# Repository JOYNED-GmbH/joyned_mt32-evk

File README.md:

This is a hardware reference design for a fully compliant and certified Milan endpoint. It converts from a AVB/Milan network to I2S or TDM and vice versa.
Please feel free to copy and modify for your individual needs. This hardware reference design is published under the Creative Commons License. 

For software licensing visit www.joyned.io/oem-and-licensing

Product details: https://joyned.io/pages/mt32-oem-milan-endpoint

Portmap Spreadsheet: https://files.joyned.io/documents/mt32-evk/JOYNED_xCORE-200-Devices-Package-and-Portmap_AvbModule_MT32.xlsx

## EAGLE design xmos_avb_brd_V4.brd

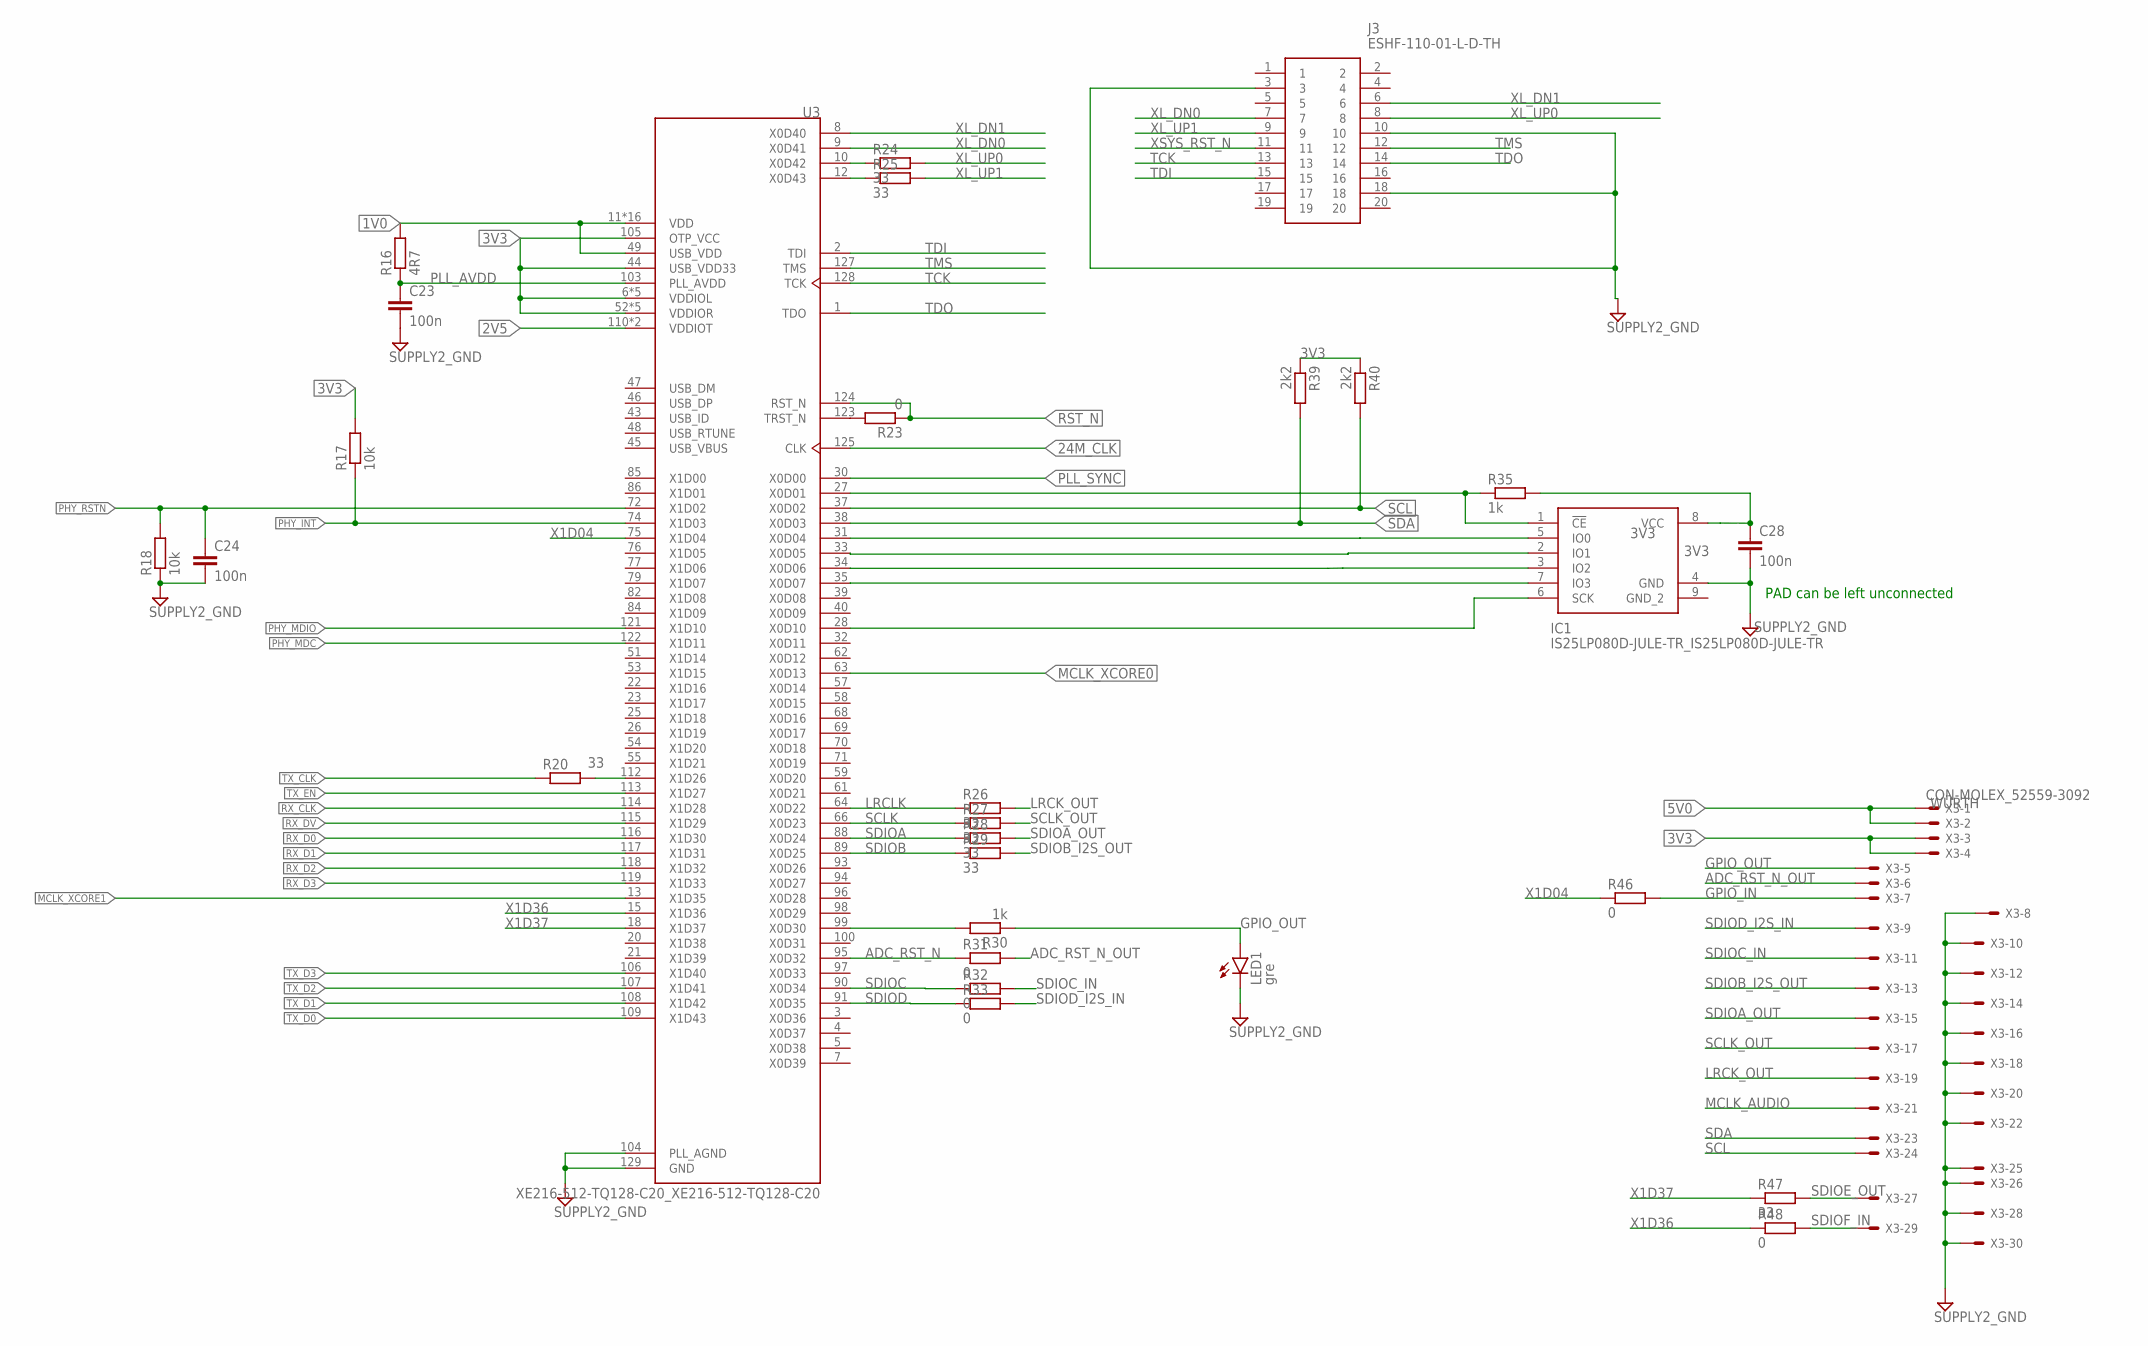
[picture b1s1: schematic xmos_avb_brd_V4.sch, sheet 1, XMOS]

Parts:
C23, C24, C28: 100n; RCL_C0402
IC1: IS25LP080D-JULE-TR_IS25LP080D-JULE-TR; IS25LP080D-JULE-TR_SON50P300X200X55-9N
J3: ESHF-110-01-L-D-TH; SHDR20W41P127_2X10_1905X559X54
LED1: gre; LED_CHIP-LED0603
R16: 4R7; RCL_R0402
R17, R18: 10k; RCL_R0402
R20, R24, R25, R26, R27, R28, R29, R47: 33; RCL_R0402
R23, R31, R32, R33, R46, R48: 0; RCL_R0402
R30, R35: 1k; RCL_R0402
R39, R40: 2k2; RCL_R0402
U3: XE216-512-TQ128-C20_XE216-512-TQ128-C20; XE216-512-TQ128-C20_QFP40P1600X1600X120-129N
X3: CON-MOLEX_52559-3092; MPN 687330124422

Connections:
1V0: R16.2, U3.11 (VDD), U3.16 (VDD), U3.17 (VDD), U3.24 (VDD), U3.36 (VDD), U3.41 (VDD), U3.49 (USB_VDD), U3.56 (VDD), U3.60 (VDD), U3.73 (VDD), U3.80 (VDD), U3.81 (VDD), U3.87 (VDD), U3.101 (VDD), U3.102 (VDD), U3.120 (VDD), U3.126 (VDD); also elsewhere on the board
2V5: U3.110 (VDDIOT), U3.111 (VDDIOT); also elsewhere on the board
3V3: C28.1, IC1.8 (VCC), R17.2, R35.2, R39.1, R40.1, U3.6 (VDDIOL), U3.14 (VDDIOL), U3.19 (VDDIOL), U3.29 (VDDIOL), U3.42 (VDDIOL), U3.44 (USB_VDD33), U3.52 (VDDIOR), U3.67 (VDDIOR), U3.78 (VDDIOR), U3.83 (VDDIOR), U3.92 (VDDIOR), U3.105 (OTP_VCC), X3.3, X3.4; also elsewhere on the board
5V0: X3.1, X3.2; also elsewhere on the board
24M_CLK: U3.125 (CLK); also elsewhere on the board
ADC_RST_N: R31.1, U3.95 (X0D32)
ADC_RST_N_OUT: R31.2, X3.6
GND: C23.2, C24.2, C28.2, IC1.4 (GND), J3.3, J3.10, J3.18, LED1.C, R18.1, U3.104 (PLL_AGND), U3.129 (GND), X3.8, X3.10, X3.12, X3.14, X3.16, X3.18, X3.20, X3.22, X3.25, X3.26, X3.28, X3.30; also elsewhere on the board
GPIO_IN: R46.2, X3.7
GPIO_OUT: LED1.A, R30.1, X3.5
LRCK_OUT: R26.2, X3.19
LRCLK: R26.1, U3.64 (X0D22)
MCLK_AUDIO: X3.21; also elsewhere on the board
MCLK_XCORE0: U3.63 (X0D13); also elsewhere on the board
MCLK_XCORE1: U3.13 (X1D35); also elsewhere on the board
unnamed: R30.2, U3.99 (X0D30)
unnamed: IC1.6 (SCK), U3.28 (X0D10)
unnamed: IC1.5 (IO0), U3.31 (X0D04)
unnamed: IC1.2 (IO1), U3.33 (X0D05)
unnamed: IC1.3 (IO2), U3.34 (X0D06)
unnamed: R20.2, U3.112 (X1D26)
unnamed: IC1.7 (IO3), U3.35 (X0D07)
unnamed: R24.1, U3.10 (X0D42)
unnamed: R25.1, U3.12 (X0D43)
unnamed: R23.2, U3.123 (TRST_N)
PHY_INT: R17.1, U3.74 (X1D03); also elsewhere on the board
PHY_MDC: U3.122 (X1D11); also elsewhere on the board
PHY_MDIO: U3.121 (X1D10); also elsewhere on the board
PHY_RSTN: C24.1, R18.2, U3.72 (X1D02); also elsewhere on the board
PLL_AVDD: C23.1, R16.1, U3.103 (PLL_AVDD)
PLL_SYNC: U3.30 (X0D00); also elsewhere on the board
RST_N: R23.1, U3.124 (RST_N); also elsewhere on the board
RX_CLK: U3.114 (X1D28); also elsewhere on the board
RX_D0: U3.116 (X1D30); also elsewhere on the board
RX_D1: U3.117 (X1D31); also elsewhere on the board
RX_D2: U3.118 (X1D32); also elsewhere on the board
RX_D3: U3.119 (X1D33); also elsewhere on the board
RX_DV: U3.115 (X1D29); also elsewhere on the board
SCL: R40.2, U3.37 (X0D02), X3.24; also elsewhere on the board
SCLK: R27.1, U3.66 (X0D23)
SCLK_OUT: R27.2, X3.17
SDA: R39.2, U3.38 (X0D03), X3.23; also elsewhere on the board
SDIOA: R28.1, U3.88 (X0D24)
SDIOA_OUT: R28.2, X3.15
SDIOB: R29.1, U3.89 (X0D25)
SDIOB_I2S_OUT: R29.2, X3.13
SDIOC: R32.1, U3.90 (X0D34)
SDIOC_IN: R32.2, X3.11
SDIOD: R33.1, U3.91 (X0D35)
SDIOD_I2S_IN: R33.2, X3.9
SDIOE_OUT: R47.2, X3.27
SDIOF_IN: R48.2, X3.29
SPI_CS: IC1.1 (!CE), R35.1, U3.27 (X0D01)
TCK: J3.13, U3.128 (TCK)
TDI: J3.15, U3.2 (TDI)
TDO: J3.14, U3.1 (TDO)
TMS: J3.12, U3.127 (TMS)
TX_CLK: R20.1; also elsewhere on the board
TX_D0: U3.109 (X1D43); also elsewhere on the board
TX_D1: U3.108 (X1D42); also elsewhere on the board
TX_D2: U3.107 (X1D41); also elsewhere on the board
TX_D3: U3.106 (X1D40); also elsewhere on the board
TX_EN: U3.113 (X1D27); also elsewhere on the board
X1D04: R46.1, U3.75 (X1D04)
X1D36: R48.1, U3.15 (X1D36)
X1D37: R47.1, U3.18 (X1D37)
XL_DN0: J3.7, U3.9 (X0D41)
XL_DN1: J3.6, U3.8 (X0D40)
XL_UP0: J3.8, R24.2
XL_UP1: J3.9, R25.2
XSYS_RST_N: J3.11; also elsewhere on the board

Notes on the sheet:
PAD can be left unconnected

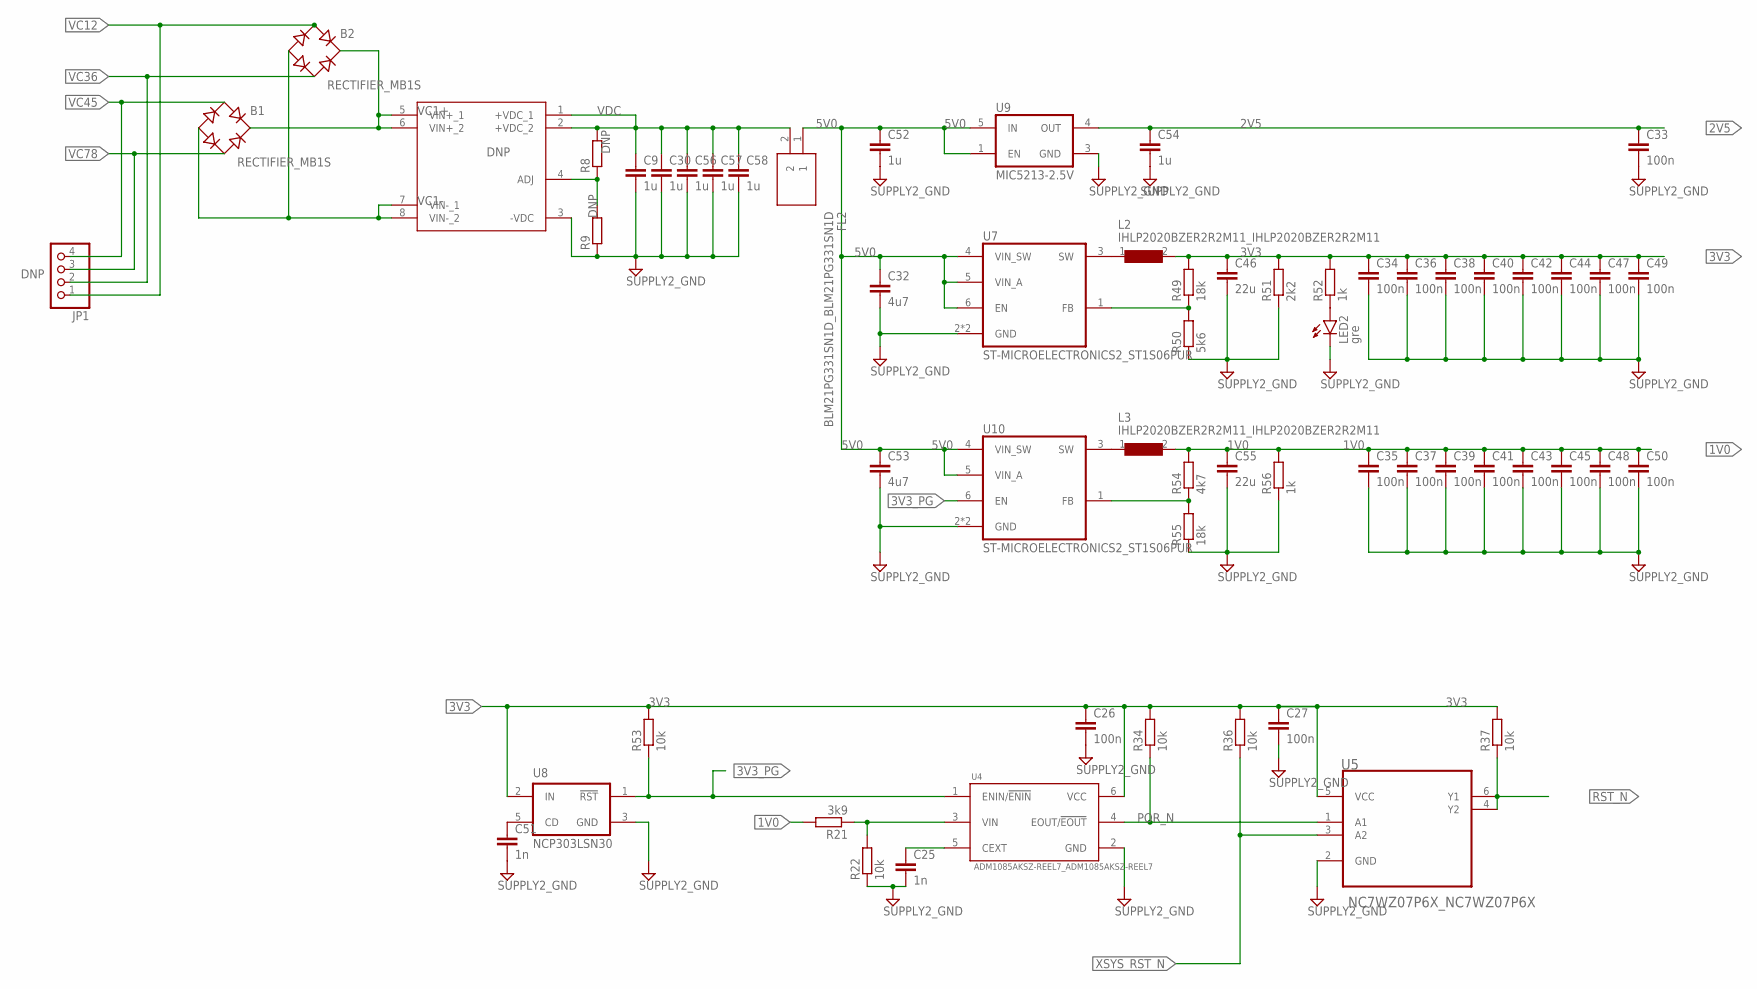
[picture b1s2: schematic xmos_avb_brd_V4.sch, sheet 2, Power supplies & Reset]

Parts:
B1, B2: RECTIFIER_MB1S; RECTIFIER_SOIC-4
C9, C30, C52, C54, C56, C57, C58: 1u; RCL_C1206
C25, C51: 1n; RCL_C0402
C26, C27, C33, C34, C35, C36, C37, C38, C39, C40, C41, C42, C43, C44, C45, C47, C48, C49, C50: 100n; RCL_C0402
C32, C53: 4u7; RCL_C1206
C46, C55: 22u; RCL_C1206
FL2: BLM21PG331SN1D_BLM21PG331SN1D; BLM21PG331SN1D_BEADC2012X105N
JP1: PINHEAD_PINHD-1X4; PINHEAD_1X04
L2, L3: IHLP2020BZER2R2M11_IHLP2020BZER2R2M11; IHLP2020BZER2R2M11_INDPM5552X200N
LED2: gre; LED_CHIP-LED0603
R8, R9: RCL_R-EU_R0402; RCL_R0402
R21: 3k9; RCL_R0402
R22, R34, R36, R37, R53: 10k; RCL_R0402
R49, R55: 18k; RCL_R0402
R50: 5k6; RCL_R0402
R51: 2k2; RCL_R0402
R52, R56: 1k; RCL_R0402
R54: 4k7; RCL_R0402
U1: AG9900_AG9905LP; AG9900_AG9900LP
U4: ADM1085AKSZ-REEL7_ADM1085AKSZ-REEL7; ADM1085AKSZ-REEL7_SOP65P210X95-6N
U5: NC7WZ07P6X_NC7WZ07P6X; NC7WZ07P6X_SOT65P210X110-6N
U7, U10: ST-MICROELECTRONICS2_ST1S06PUR; ST-MICROELECTRONICS2_DFN6
U8: NCP303LSN30; ON-SEMI_SOT23-5
U9: MIC5213-2.5V; MICREL2_SC70-5

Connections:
1V0: C35.1, C37.1, C39.1, C41.1, C43.1, C45.1, C48.1, C50.1, C55.1, L3.2, R21.2, R54.2, R56.2; also elsewhere on the board
2V5: C33.1, C54.1, U9.4 (OUT); also elsewhere on the board
3V3: C26.1, C27.1, C34.1, C36.1, C38.1, C40.1, C42.1, C44.1, C46.1, C47.1, C49.1, L2.2, R34.2, R36.2, R37.2, R49.2, R51.2, R52.2, R53.2, U4.6 (VCC), U5.5 (VCC), U8.2 (IN); also elsewhere on the board
3V3_PG: R53.1, U4.1 (ENIN/!ENIN), U8.1 (!RST!), U10.6 (EN)
5V0: C32.1, C52.1, C53.1, FL2.1, U7.4 (VIN_SW), U7.5 (VIN_A), U7.6 (EN), U9.1 (EN), U9.5 (IN), U10.4 (VIN_SW), U10.5 (VIN_A); also elsewhere on the board
GND: C9.2, C25.2, C26.2, C27.2, C30.2, C32.2, C33.2, C34.2, C35.2, C36.2, C37.2, C38.2, C39.2, C40.2, C41.2, C42.2, C43.2, C44.2, C45.2, C46.2, C47.2, C48.2, C49.2, C50.2, C51.2, C52.2, C53.2, C54.2, C55.2, C56.2, C57.2, C58.2, LED2.C, R9.1, R22.1, R50.1, R51.1, R55.1, R56.1, U1.3 (-VDC), U4.2 (GND), U5.2 (GND), U7.2 (GND), U7.7 (GND), U8.3 (GND), U9.3 (GND), U10.2 (GND), U10.7 (GND); also elsewhere on the board
unnamed: R21.1, R22.2, U4.3 (VIN)
unnamed: R8.1, R9.2, U1.4 (ADJ)
unnamed: L2.1, U7.3 (SW)
unnamed: L3.1, U10.3 (SW)
unnamed: C25.1, U4.5 (CEXT)
unnamed: R54.1, R55.2, U10.1 (FB)
unnamed: C51.1, U8.5 (CD)
unnamed: R49.1, R50.2, U7.1 (FB)
unnamed: LED2.A, R52.1
POR_N: R34.1, U4.4 (EOUT/!EOUT), U5.1 (A1)
RST_N: R37.1, U5.4 (Y2), U5.6 (Y1); also elsewhere on the board
VC1+: B1.+, B2.+, U1.5 (VIN+_1), U1.6 (VIN+_2)
VC1-: B1.-, B2.-, U1.7 (VIN-_1), U1.8 (VIN-_2)
VC12: B2.~1 (AC1), JP1.1; also elsewhere on the board
VC36: B2.~2 (AC2), JP1.2; also elsewhere on the board
VC45: B1.~1 (AC1), JP1.4; also elsewhere on the board
VC78: B1.~2 (AC2), JP1.3; also elsewhere on the board
VDC: C9.1, C30.1, C56.1, C57.1, C58.1, FL2.2, R8.2, U1.1 (+VDC_1), U1.2 (+VDC_2)
XSYS_RST_N: R36.1, U5.3 (A2); also elsewhere on the board

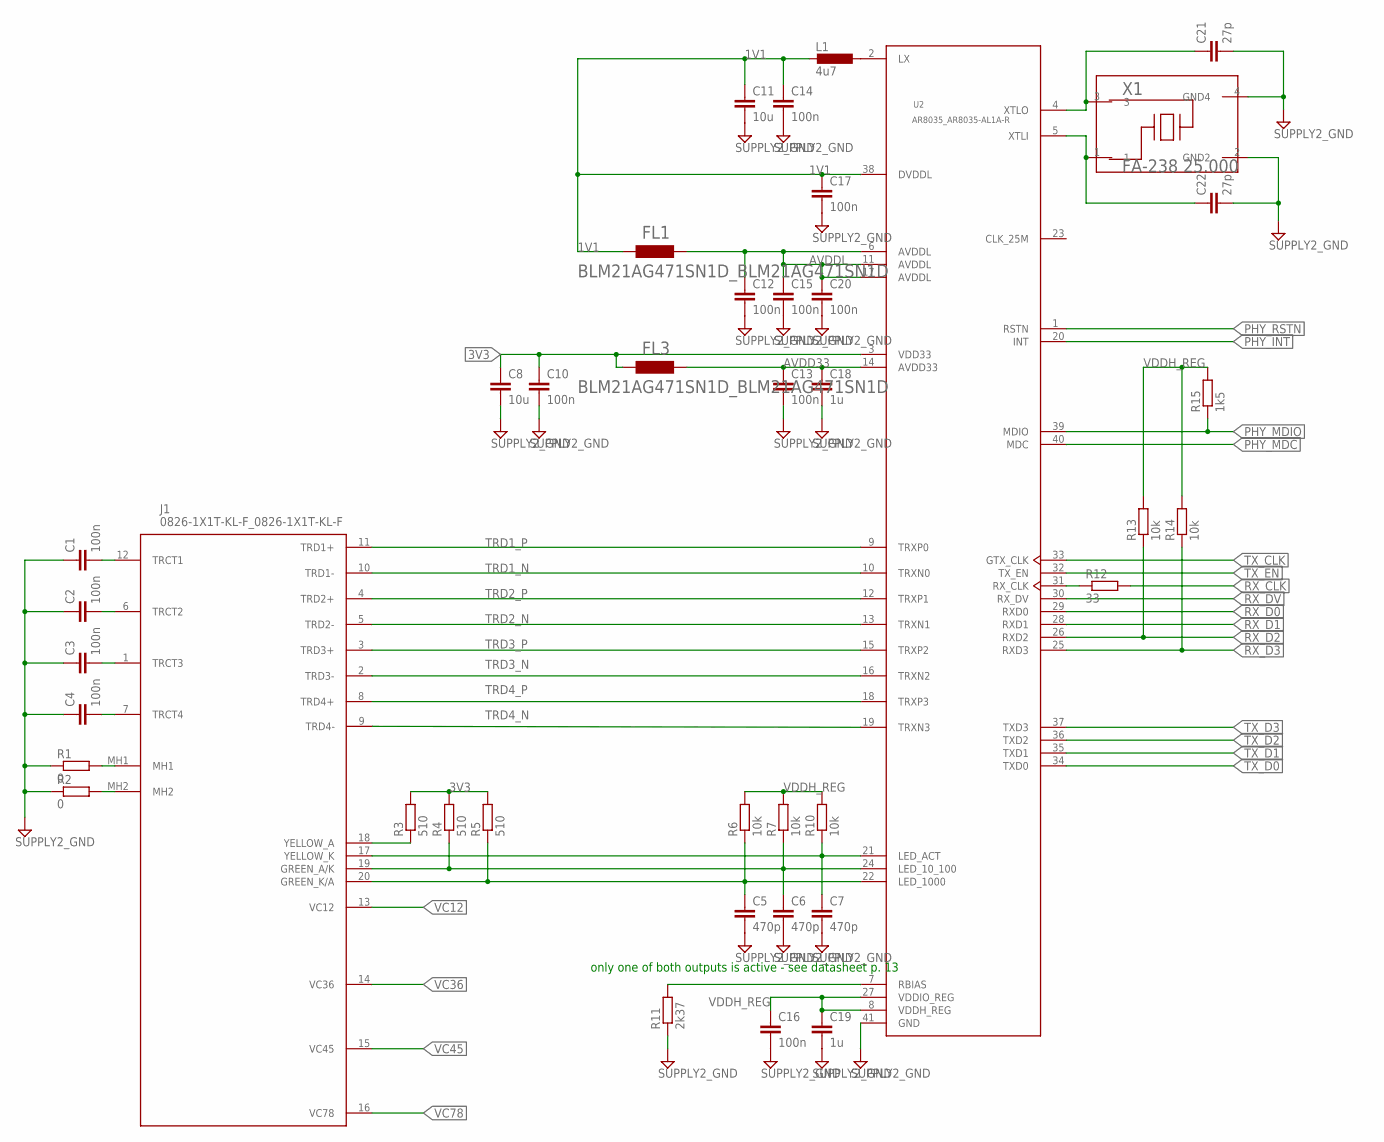
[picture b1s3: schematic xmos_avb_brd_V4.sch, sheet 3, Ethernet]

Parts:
C1, C2, C3, C4, C10, C12, C13, C14, C15, C16, C17, C20: 100n; RCL_C0402
C5, C6, C7: 470p; RCL_C0402
C8, C11: 10u; RCL_C1206
C18, C19: 1u; RCL_C1206
C21, C22: 27p; RCL_C0402
FL1, FL3: BLM21AG471SN1D_BLM21AG471SN1D; BLM21AG471SN1D_BEADC2012X105N
J1: 0826-1X1T-KL-F_0826-1X1T-KL-F; 0826-1X1T-KL-F_08261X1TKLF
L1: 4u7; RCL_L2012C
R1, R2: 0; RCL_R0402
R3, R4, R5: 510; RCL_R0402
R6, R7, R10, R13, R14: 10k; RCL_R0402
R11: 2k37; RCL_R0402
R12: 33; RCL_R0402
R15: 1k5; RCL_R0402
U2: AR8035_AR8035-AL1A-R; AR8035_QFN40P500X500X75-41N
X1: FA-238 25.000; FA-238_OSCCC320X250X70-4N

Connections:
1V1: C11.1, C14.1, C17.1, FL1.1, L1.2, U2.38 (DVDDL)
3V3: C8.1, C10.1, FL3.1, R3.2, R4.2, R5.2, U2.3 (VDD33); also elsewhere on the board
AVDD33: C13.1, C18.1, FL3.2, U2.14 (AVDD33)
AVDDL: C12.1, C15.1, C20.1, FL1.2, U2.6 (AVDDL), U2.11 (AVDDL), U2.17 (AVDDL)
GND: C1.1, C2.1, C3.1, C4.1, C5.2, C6.2, C7.2, C8.2, C10.2, C11.2, C12.2, C13.2, C14.2, C15.2, C16.2, C17.2, C18.2, C19.2, C20.2, C21.2, C22.2, R1.1, R2.1, R11.1, U2.41 (GND), X1.2 (GND2), X1.4 (GND4); also elsewhere on the board
unnamed: L1.1, U2.2 (LX)
unnamed: J1.MH1, R1.2
unnamed: C6.1, J1.19 (GREEN_A/K), R4.1, R7.1, U2.24 (LED_10_100)
unnamed: J1.18 (YELLOW_A), R3.1
unnamed: C21.1, U2.4 (XTLO), X1.3
unnamed: C22.1, U2.5 (XTLI), X1.1
unnamed: R12.1, U2.31 (RX_CLK)
unnamed: C7.1, J1.17 (YELLOW_K), R10.1, U2.21 (LED_ACT)
unnamed: C1.2, J1.12 (TRCT1)
unnamed: C2.2, J1.6 (TRCT2)
unnamed: R11.2, U2.7 (RBIAS)
unnamed: C5.1, J1.20 (GREEN_K/A), R5.1, R6.1, U2.22 (LED_1000)
unnamed: C3.2, J1.1 (TRCT3)
unnamed: C4.2, J1.7 (TRCT4)
unnamed: J1.MH2, R2.2
PHY_INT: U2.20 (INT); also elsewhere on the board
PHY_MDC: U2.40 (MDC); also elsewhere on the board
PHY_MDIO: R15.1, U2.39 (MDIO); also elsewhere on the board
PHY_RSTN: U2.1 (RSTN); also elsewhere on the board
RX_CLK: R12.2; also elsewhere on the board
RX_D0: U2.29 (RXD0); also elsewhere on the board
RX_D1: U2.28 (RXD1); also elsewhere on the board
RX_D2: R13.1, U2.26 (RXD2); also elsewhere on the board
RX_D3: R14.1, U2.25 (RXD3); also elsewhere on the board
RX_DV: U2.30 (RX_DV); also elsewhere on the board
TRD1_N: J1.10 (TRD1-), U2.10 (TRXN0)
TRD1_P: J1.11 (TRD1+), U2.9 (TRXP0)
TRD2_N: J1.5 (TRD2-), U2.13 (TRXN1)
TRD2_P: J1.4 (TRD2+), U2.12 (TRXP1)
TRD3_N: J1.2 (TRD3-), U2.16 (TRXN2)
TRD3_P: J1.3 (TRD3+), U2.15 (TRXP2)
TRD4_N: J1.9 (TRD4-), U2.19 (TRXN3)
TRD4_P: J1.8 (TRD4+), U2.18 (TRXP3)
TX_CLK: U2.33 (GTX_CLK); also elsewhere on the board
TX_D0: U2.34 (TXD0); also elsewhere on the board
TX_D1: U2.35 (TXD1); also elsewhere on the board
TX_D2: U2.36 (TXD2); also elsewhere on the board
TX_D3: U2.37 (TXD3); also elsewhere on the board
TX_EN: U2.32 (TX_EN); also elsewhere on the board
VC12: J1.13 (VC12); also elsewhere on the board
VC36: J1.14 (VC36); also elsewhere on the board
VC45: J1.15 (VC45); also elsewhere on the board
VC78: J1.16 (VC78); also elsewhere on the board
VDDH_REG: C16.1, C19.1, R6.2, R7.2, R10.2, R13.2, R14.2, R15.2, U2.8 (VDDH_REG), U2.27 (VDDIO_REG)

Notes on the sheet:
only one of both outputs is active - see datasheet p. 13

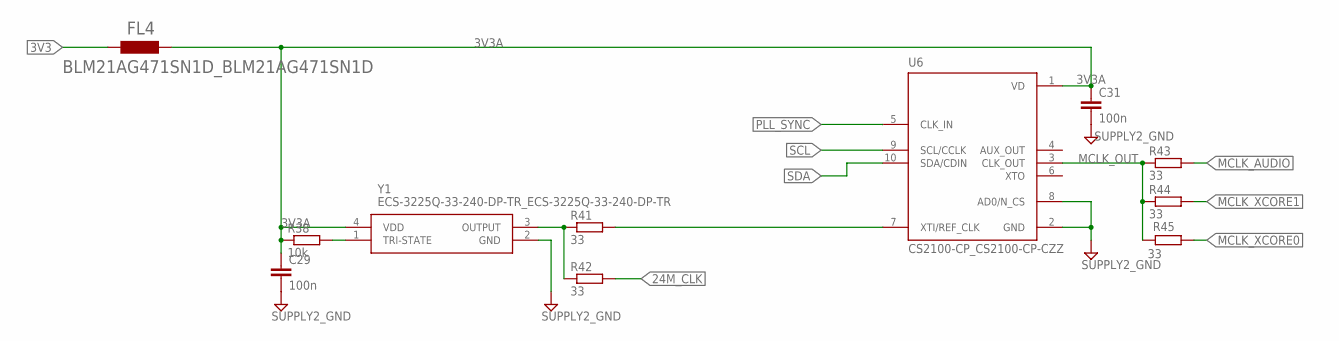
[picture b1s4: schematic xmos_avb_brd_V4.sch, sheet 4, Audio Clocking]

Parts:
C29, C31: 100n; RCL_C0402
FL4: BLM21AG471SN1D_BLM21AG471SN1D; BLM21AG471SN1D_BEADC2012X105N
R38: 10k; RCL_R0402
R41, R42, R43, R44, R45: 33; RCL_R0402
U6: CS2100-CP_CS2100-CP-CZZ; CS2100-CP_CIRRUS-LOGIC_MSOP10
Y1: ECS-3225Q-33-240-DP-TR_ECS-3225Q-33-240-DP-TR; ECS-3225Q-33-240-DP-TR_ECS3225Q33240DPTR

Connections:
3V3: FL4.1; also elsewhere on the board
3V3A: C29.1, C31.1, FL4.2, R38.1, U6.1 (VD), Y1.4 (VDD)
24M_CLK: R42.2; also elsewhere on the board
GND: C29.2, C31.2, U6.2 (GND), U6.8 (AD0/N_CS), Y1.2 (GND); also elsewhere on the board
MCLK_AUDIO: R43.2; also elsewhere on the board
MCLK_OUT: R43.1, R44.1, R45.2, U6.3 (CLK_OUT)
MCLK_XCORE0: R45.1; also elsewhere on the board
MCLK_XCORE1: R44.2; also elsewhere on the board
unnamed: R41.1, R42.1, Y1.3 (OUTPUT)
unnamed: R41.2, U6.7 (XTI/REF_CLK)
unnamed: R38.2, Y1.1 (TRI-STATE)
PLL_SYNC: U6.5 (CLK_IN); also elsewhere on the board
SCL: U6.9 (SCL/CCLK); also elsewhere on the board
SDA: U6.10 (SDA/CDIN); also elsewhere on the board

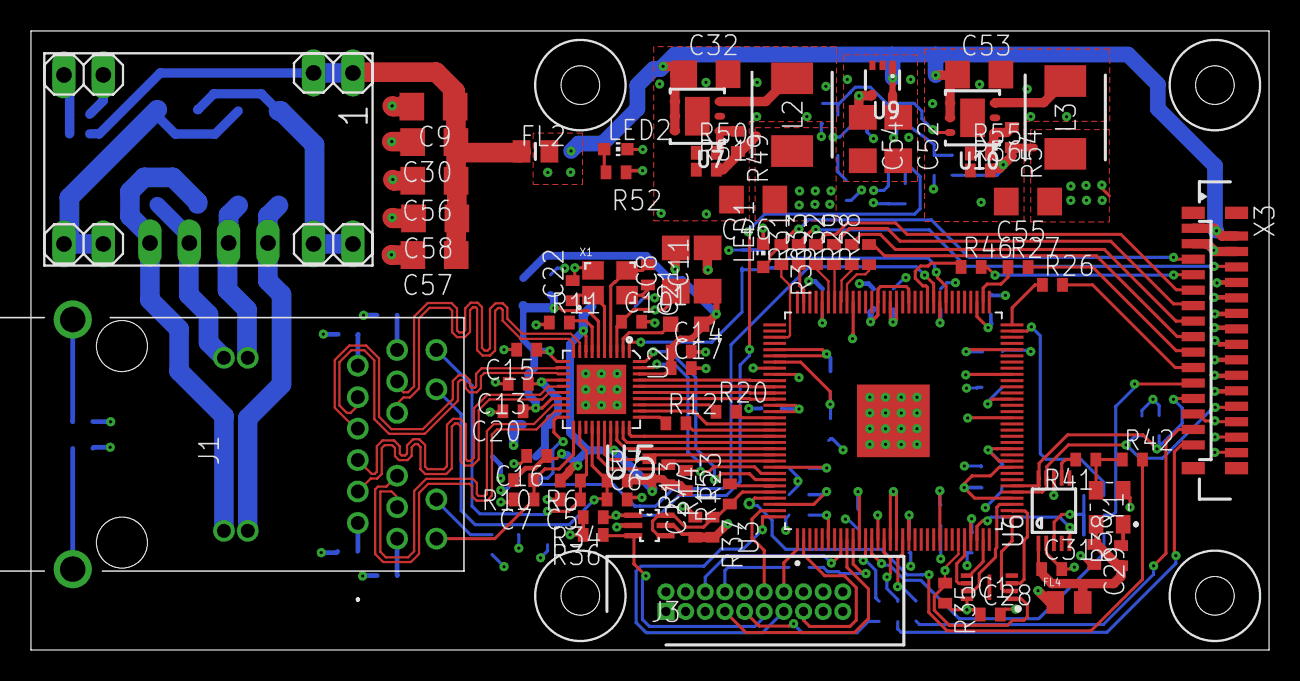
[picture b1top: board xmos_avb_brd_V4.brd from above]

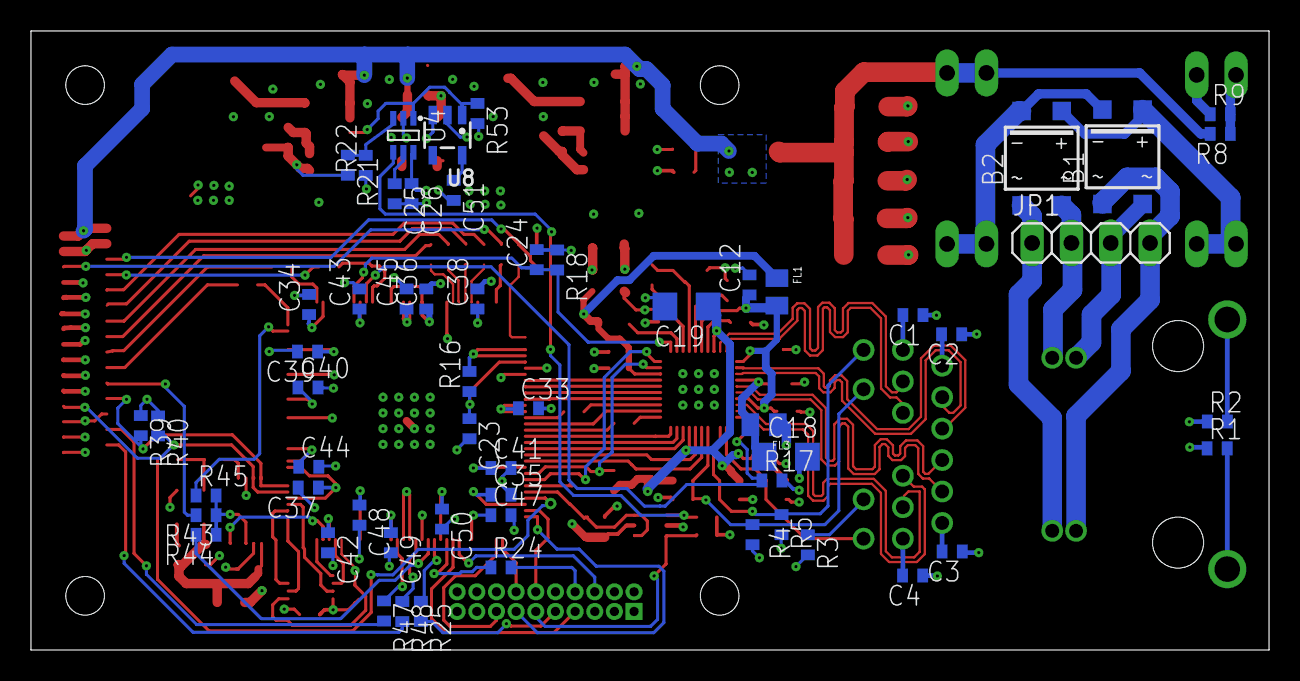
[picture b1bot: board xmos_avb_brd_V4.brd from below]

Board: 4 copper layers, 80.0 x 40.0 mm, 145 parts (58 on the bottom side), 121 nets.

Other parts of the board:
U$4, U$5, U$6, U$7: DRIL-2,5

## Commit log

2025-08-20 Link to Portmap Spreadsheet added to Docu
2025-11-14 new debug header added to improve debugging with xmos. old tag-connect removed.
2025-11-14 ksz9131 added to schematic.#
2025-11-17 layout wip
2025-11-17 resolved DRC errors and exported manufacturing data for V4.
2025-11-17 final manufacturing data
2026-04-23 Revise licensing info and add product details
    Updated software licensing link and added product details.
2026-04-23 Fix typo in product details link
2026-04-23 Update README to specify certified Milan endpoint
    Clarified that the Milan endpoint is certified.
2026-04-23 Update Portmap Spreadsheet link in README
2026-04-23 Fix URL for Portmap Spreadsheet in README
